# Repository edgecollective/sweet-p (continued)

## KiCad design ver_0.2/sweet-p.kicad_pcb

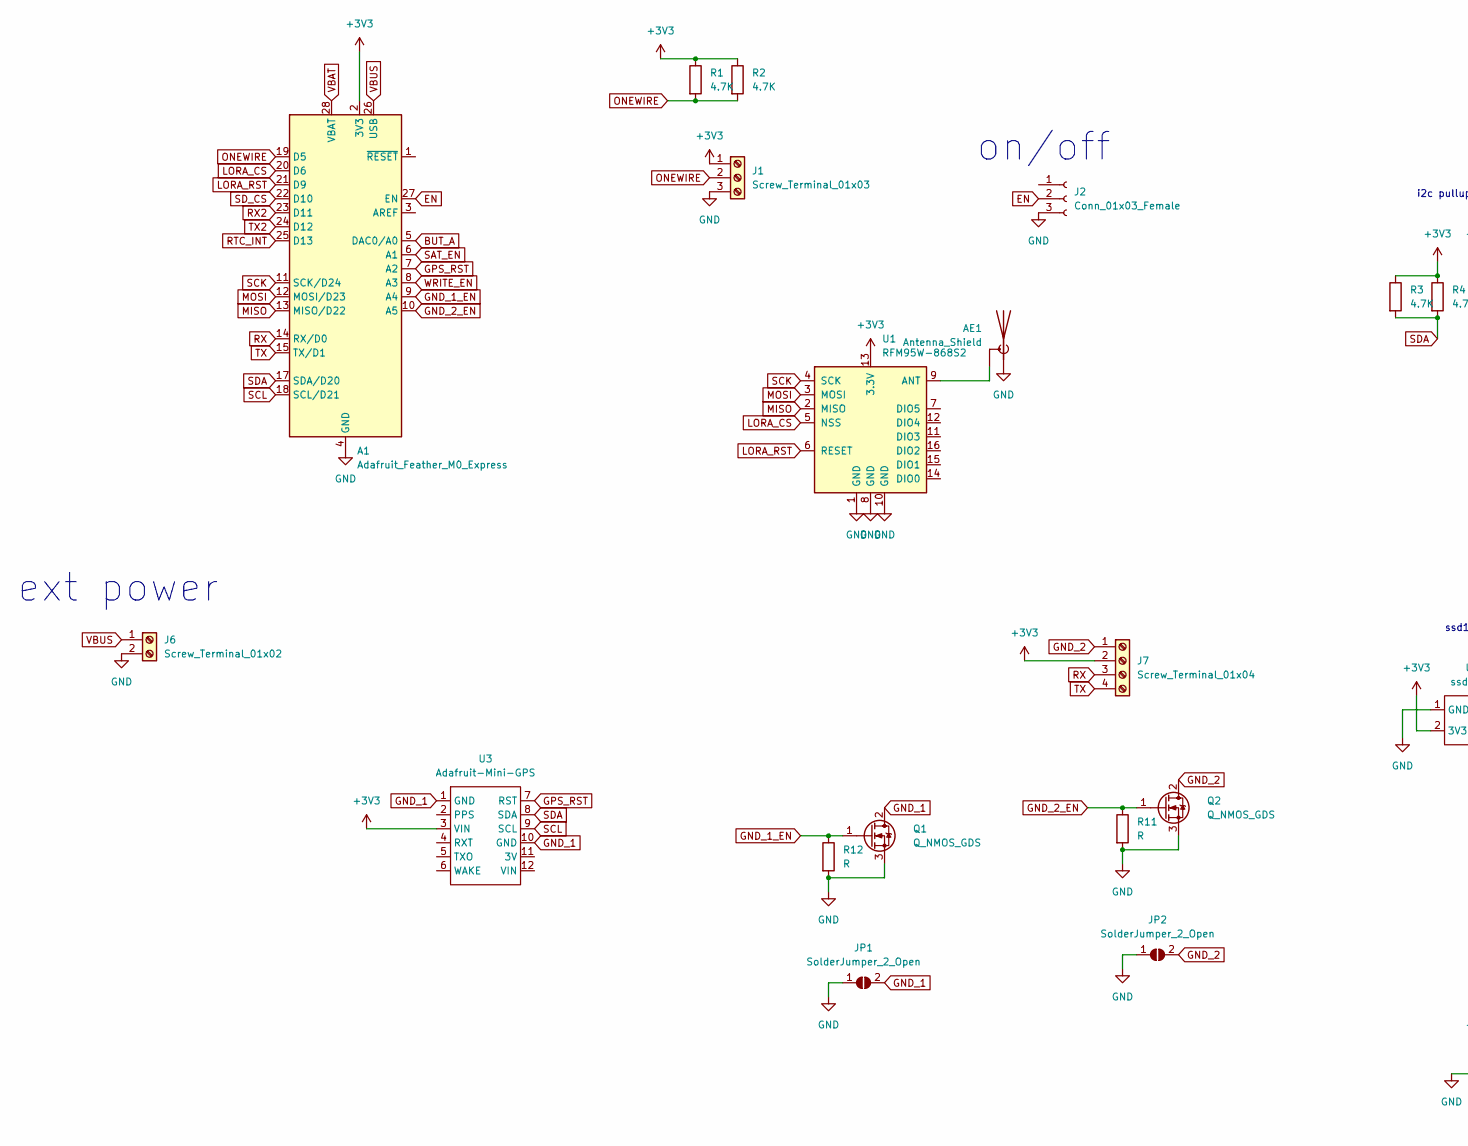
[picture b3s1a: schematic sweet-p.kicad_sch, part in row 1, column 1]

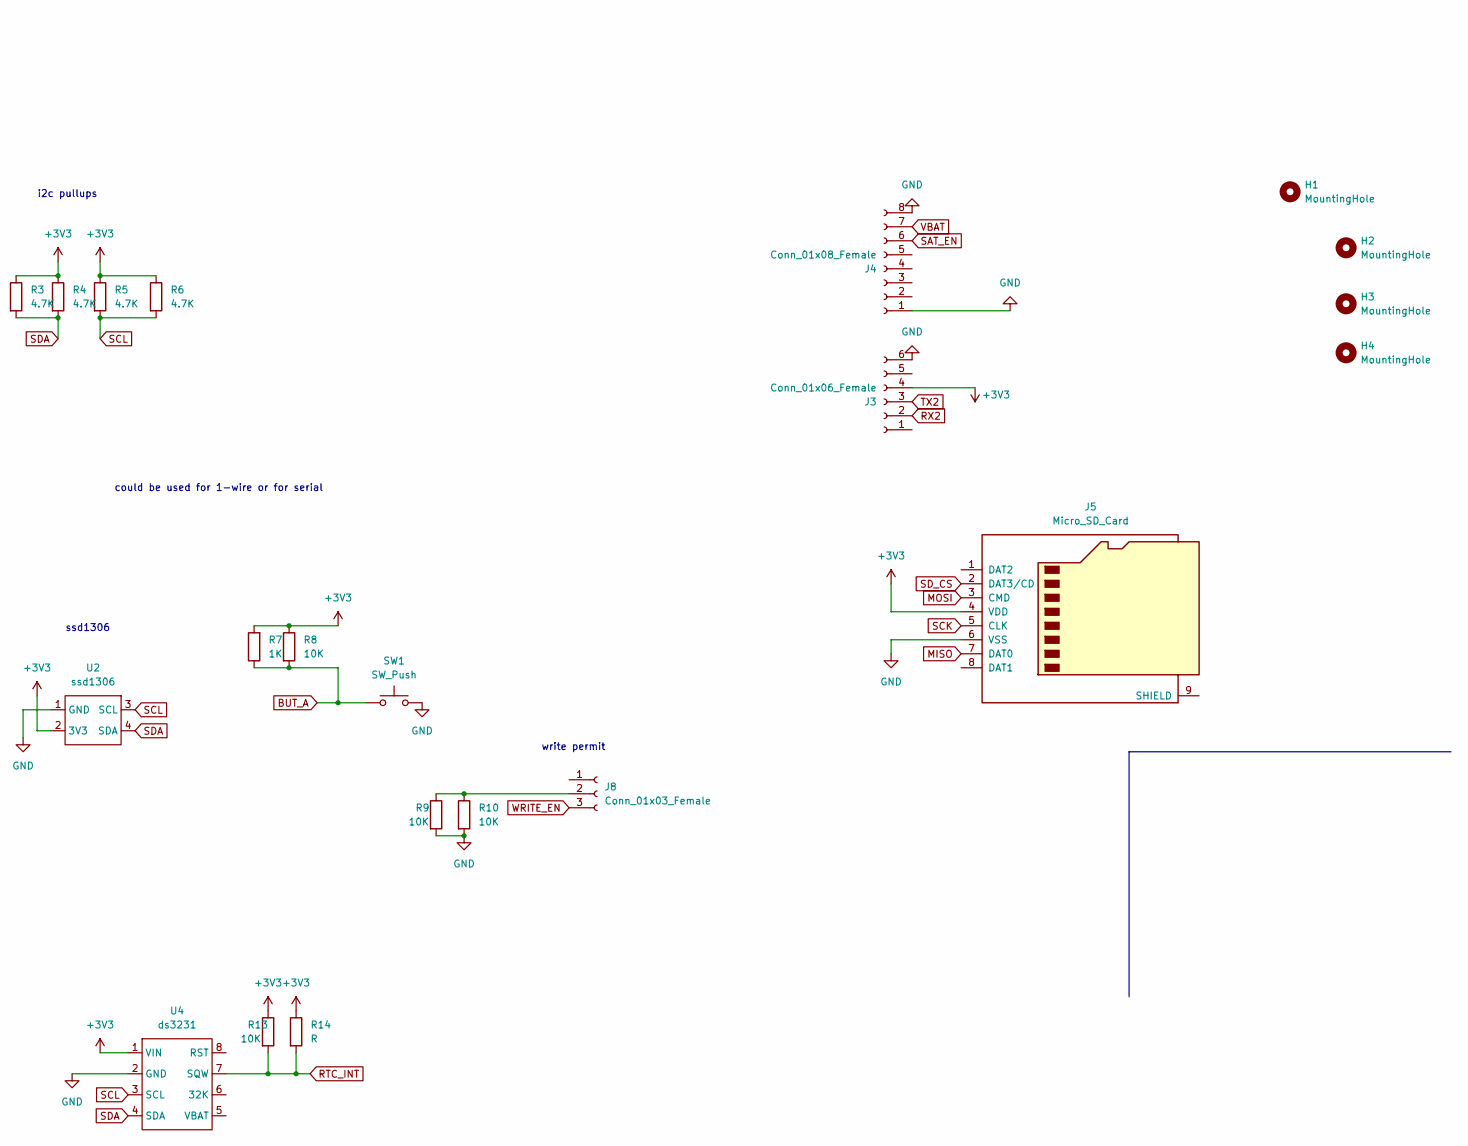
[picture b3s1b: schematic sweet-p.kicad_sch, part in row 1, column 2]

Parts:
A1: Adafruit_Feather_M0_Express; Adafruit_Feather
AE1: Antenna_Shield; RF_SMA_Vertical_5-1814832-1
H1, H2, H3, H4: MountingHole; MountingHole_3.2mm_M3
J1: Screw_Terminal_01x03; TerminalBlock_Phoenix_PT-1,5-3-5.0-H_1x03_P5.00mm_Horizontal
J2, J8: Conn_01x03_Female; PinSocket_1x03_P2.54mm_Vertical
J3: Conn_01x06_Female; PinSocket_1x06_P2.54mm_Vertical
J4: Conn_01x08_Female; PinSocket_1x08_P2.54mm_Vertical
J5: Micro_SD_Card; DM3D-SF_outline
J6: Screw_Terminal_01x02; TerminalBlock_Phoenix_PT-1,5-2-5.0-H_1x02_P5.00mm_Horizontal
J7: Screw_Terminal_01x04; TerminalBlock_Phoenix_PT-1,5-4-5.0-H_1x04_P5.00mm_Horizontal
JP1, JP2: SolderJumper_2_Open; SolderJumper-2_P1.3mm_Open_Pad1.0x1.5mm
Q1, Q2: Q_NMOS_GDS; SOT-23
R1, R3, R6: 4.7K; R_Axial_DIN0204_L3.6mm_D1.6mm_P7.62mm_Horizontal
R2, R4, R5: 4.7K; R_0603_1608Metric_Pad0.98x0.95mm_HandSolder
R7: 1K; R_0603_1608Metric_Pad0.98x0.95mm_HandSolder
R8, R9: 10K; R_Axial_DIN0204_L3.6mm_D1.6mm_P7.62mm_Horizontal
R10, R13: 10K; R_0603_1608Metric_Pad0.98x0.95mm_HandSolder
R11, R12: R; R_0603_1608Metric_Pad0.98x0.95mm_HandSolder
R14: R; R_Axial_DIN0204_L3.6mm_D1.6mm_P7.62mm_Horizontal
SW1: SW_Push; SW_Tactile_SPST_Angled_PTS645Vx31-2LFS
U1: RFM95W-868S2; HOPERF_RFM9XW_SMD
U2: ssd1306; ssd1306_a
U3: Adafruit-Mini-GPS; adafruit_mini_gps
U4: ds3231; ds3231_adafruit_breakout

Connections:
+3V3: A1.2 (3V3), J1.1, J3.4, J5.4 (VDD), J7.2, R1.1, R2.1, R3.1, R4.1, R5.1, R6.1, R7.2, R8.1, R13.1, R14.1, U1.13 (3.3V), U2.2 (3V3), U3.3 (VIN), U4.1 (VIN)
BUT_A: A1.5 (DAC0/A0), R7.1, R8.2, SW1.1
EN: A1.27 (EN), J2.2
GND: A1.4 (GND), A1.16 (GND), AE1.1 (A), J1.3, J2.3, J3.6, J4.1, J4.8, J5.6 (VSS), J6.2, JP1.1 (A), JP2.1 (A), Q1.3 (S), Q2.3 (S), R9.2, R10.2, R11.2, R12.2, SW1.2, U1.1 (GND), U1.8 (GND), U1.10 (GND), U2.1 (GND), U4.2 (GND)
GND_1: JP1.2 (B), Q1.2 (D), U3.1 (GND), U3.10 (GND)
GND_1_EN: A1.9 (A4), Q1.1 (G), R12.1
GND_2: J7.1, JP2.2 (B), Q2.2 (D)
GND_2_EN: A1.10 (A5), Q2.1 (G), R11.1
GPS_RST: A1.7 (A2), U3.7 (RST)
LORA_CS: A1.20 (D6), U1.5 (NSS)
LORA_RST: A1.21 (D9), U1.6 (RESET)
MISO: A1.13 (MISO/D22), J5.7 (DAT0), U1.2 (MISO)
MOSI: A1.12 (MOSI/D23), J5.3 (CMD), U1.3 (MOSI)
unnamed: J8.2, R9.1, R10.1
unnamed: AE1.2 (Shield), U1.9 (ANT)
ONEWIRE: A1.19 (D5), J1.2, R1.2, R2.2
RTC_INT: A1.25 (D13), R13.2, R14.2, U4.7 (SQW)
RX: A1.14 (RX/D0), J7.3
RX2: A1.23 (D11), J3.2
SAT_EN: A1.6 (A1), J4.6
SCK: A1.11 (SCK/D24), J5.5 (CLK), U1.4 (SCK)
SCL: A1.18 (SCL/D21), R5.2, R6.2, U2.3 (SCL), U3.9 (SCL), U4.3 (SCL)
SDA: A1.17 (SDA/D20), R3.2, R4.2, U2.4 (SDA), U3.8 (SDA), U4.4 (SDA)
SD_CS: A1.22 (D10), J5.2 (DAT3/CD)
TX: A1.15 (TX/D1), J7.4
TX2: A1.24 (D12), J3.3
VBAT: A1.28 (VBAT), J4.7
VBUS: A1.26 (USB), J6.1
WRITE_EN: A1.8 (A3), J8.3

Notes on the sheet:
i2c pullups
write permit
on/off
ext power
could be used for 1-wire or for serial
ssd1306

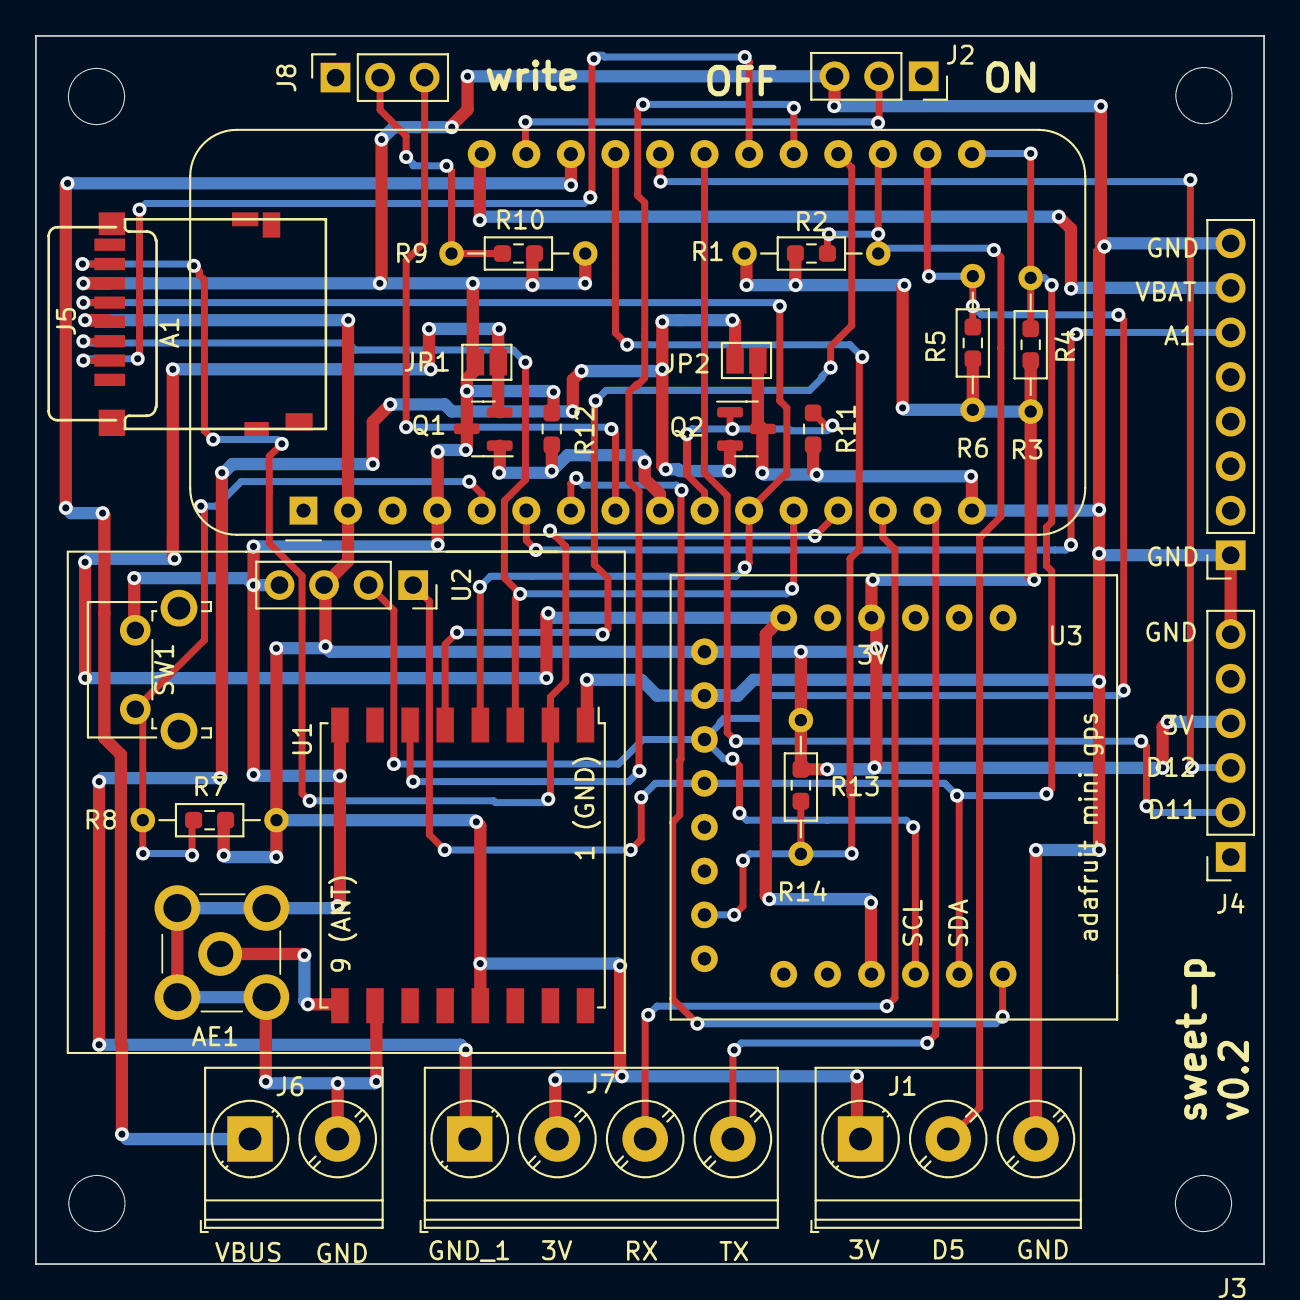
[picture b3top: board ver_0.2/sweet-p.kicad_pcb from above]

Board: 2 copper layers, 70.0 x 70.0 mm, 37 parts (1 on the bottom side), 29 nets.

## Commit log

2023-04-26 cleanup
2023-04-27 deployment version to Smithereen Farm April 27 2023
2023-05-06 laid out power
2023-05-06 fully routed
2023-07-13 reorganizing
2023-07-23 good layout -- need to check resistor locations
2023-07-23 fleshed out the power train
2023-07-23 fixed breakout
2023-07-25 continuing routing
2023-07-25 nearly all routed
2023-07-26 final layout and gerbers
2023-08-29 remote code sent to NM
2023-08-29 base sent to NM
2023-12-17 gps experiments
2023-12-18 local_only as every-minute test
2023-12-20 satellite_hour is the test code
2023-12-20 testing satellite_hour.py Dec 19 through Dec 21
2023-12-23 satellite_hour.py looks like it might work
2023-12-23 seems to be a working basic system
2023-12-23 satellite_temperature does the basic thing
2023-12-23 good candidate
2023-12-24 latest working version. added force send functionality
2024-01-09 this is a mistake
2024-01-09 Revert "this is a mistake"
    This reverts commit 5cc8ff005acb2d47508dfea686df135778592703.
2024-11-02 updated ver 0.4 sweet-p
2024-11-02 pin assignments and initial layout for ver 0.4
2024-11-02 fully routed v4
2024-11-13 good system test
2024-11-16 added force send button
2024-11-18 functional first_test.py
2024-12-21 999 recover code
2024-12-24 new depth code with trigger on d12
2025-08-14 every_few_seconds_control.py is the latest working code
2025-08-16 latch_on_alarm.py does the thing
2025-08-17 interrupt_itsy is the shizzle
2025-08-22 wakeup testing
2025-09-07 updte
2025-10-10 ver 1 completed
